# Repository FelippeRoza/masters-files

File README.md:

# masters-simulations

Files used in my master's program.

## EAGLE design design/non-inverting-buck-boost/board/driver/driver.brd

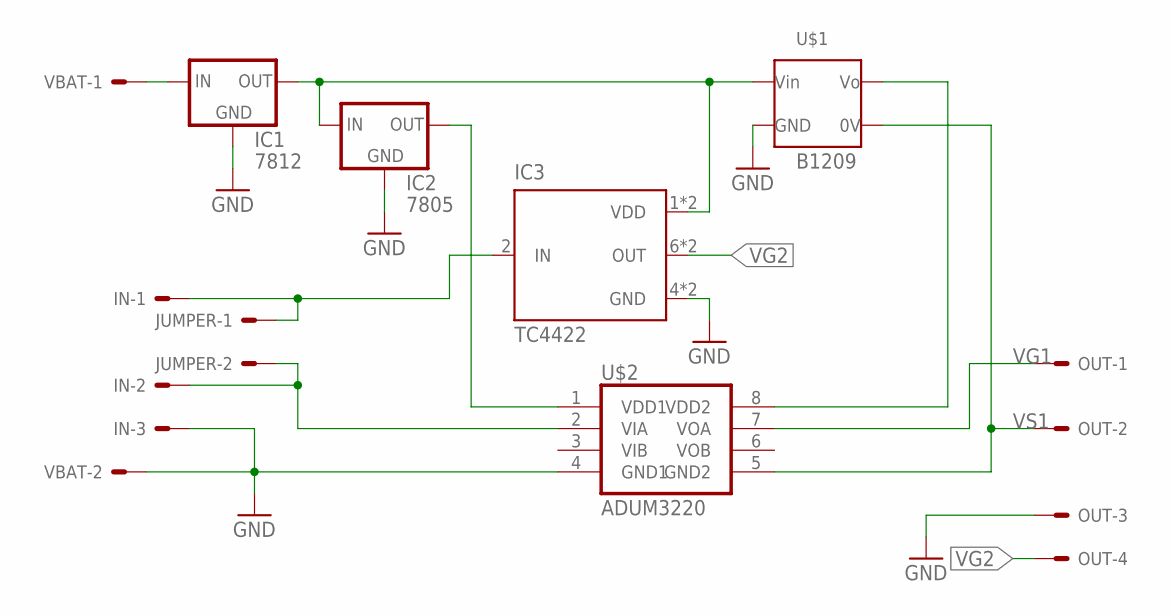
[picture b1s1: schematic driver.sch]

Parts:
IC1: 7812; 78XXS
IC2: 7805; 78XXS
IC3: TC4422; DIL08
IN: 22-23-2031
JUMPER: 22-23-2021
OUT: 22-23-2041
U$1: B1209; 22-23-2041
U$2: ADUM3220; SO8
VBAT: 22-23-2021

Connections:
5V: IC2.OUT, U$2.1 (VDD1)
12V: IC1.OUT, IC2.IN, IC3.1 (VDD), IC3.8 (VDD), U$1.2 (VIN)
GND: IC1.GND, IC2.GND, IC3.4 (GND), IC3.5 (GND), IN.3, OUT.3, U$1.1 (GND), U$2.4 (GND1), VBAT.2
unnamed: IC1.IN, VBAT.1
unnamed: IN.2, JUMPER.2, U$2.2 (VIA)
unnamed: IC3.2 (IN), IN.1, JUMPER.1
VDD2: U$1.4 (VO), U$2.8 (VDD2)
VG1: OUT.1, U$2.7 (VOA)
VG2: IC3.6 (OUT), IC3.7 (OUT), OUT.4
VS1: OUT.2, U$1.3 (0V), U$2.5 (GND2)

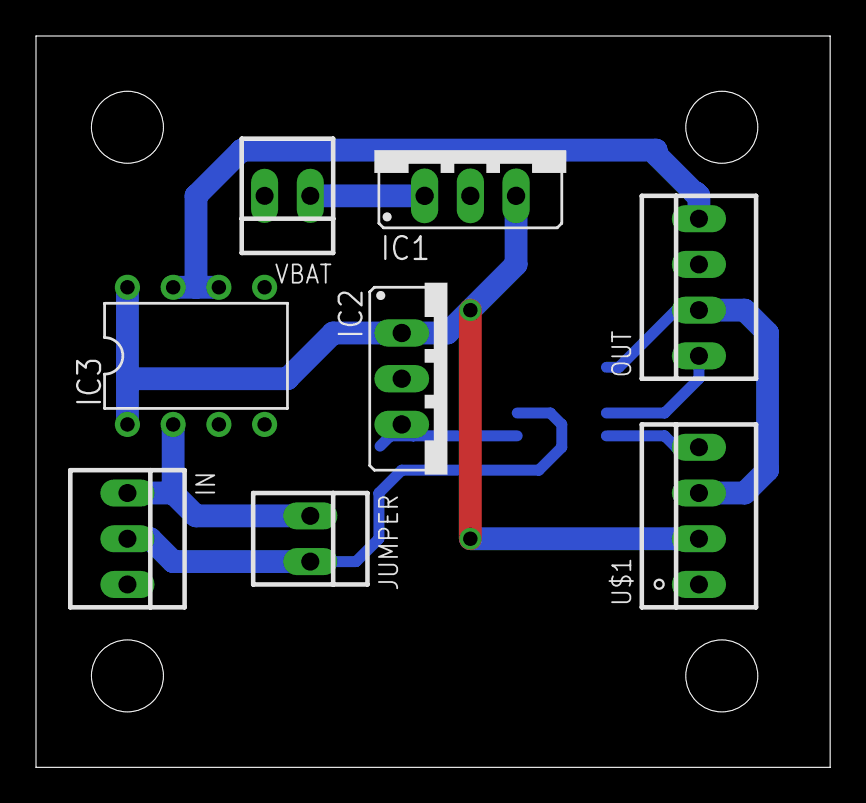
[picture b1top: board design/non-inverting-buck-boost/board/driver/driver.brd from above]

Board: 2 copper layers, 44.1 x 40.6 mm, 9 parts (1 on the bottom side), 10 nets.

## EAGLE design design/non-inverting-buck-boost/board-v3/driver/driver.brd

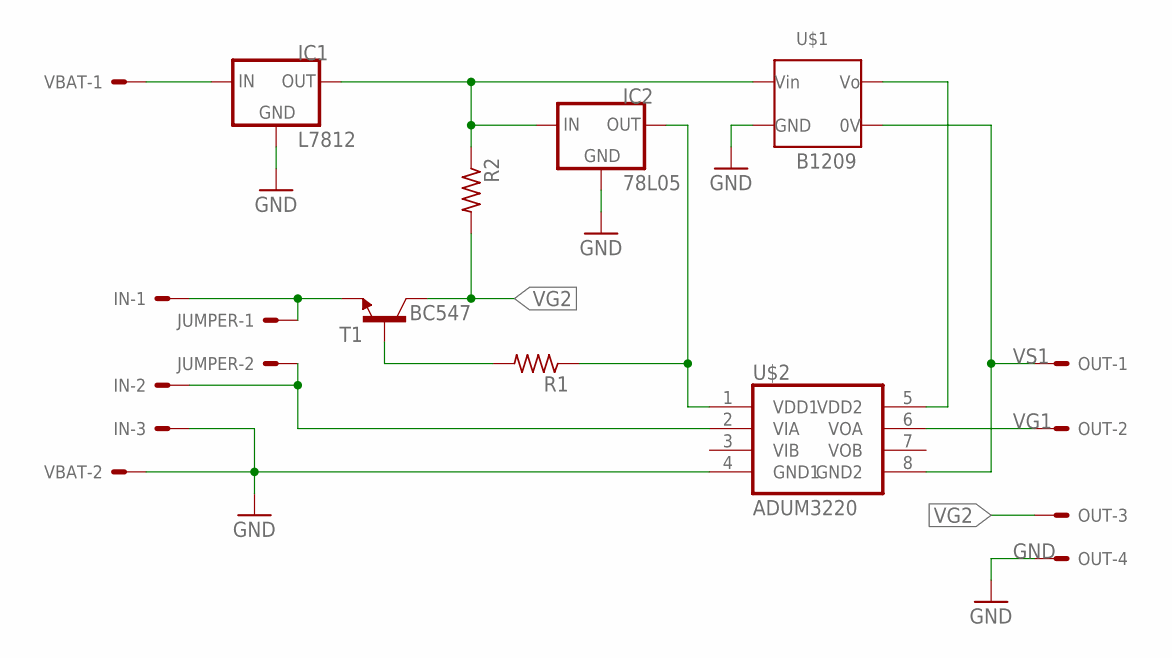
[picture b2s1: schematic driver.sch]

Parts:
IC1: L7812; 78XXL
IC2: 78L05; 78LXX
IN: 22-23-2031
JUMPER: 22-23-2021
OUT: 22-23-2041
R1, R2: R-US_0204/7; 0204/7
T1: BC547; TO92
U$1: B1209; 22-23-2041
U$2: ADUM3220; SO8
VBAT: 22-23-2021

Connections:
GND: IC1.GND, IC2.GND, IN.3, OUT.4, U$1.1 (GND), U$2.4 (GND1), VBAT.2
unnamed: IC1.OUT, IC2.IN, R2.1, U$1.2 (VIN)
unnamed: IC2.OUT, R1.1, U$2.1 (VDD1)
unnamed: R1.2, T1.2 (B)
unnamed: IC1.IN, VBAT.1
unnamed: IN.2, JUMPER.2, U$2.2 (VIA)
unnamed: IN.1, JUMPER.1, T1.1 (E)
VDD2: U$1.4 (VO), U$2.5 (VDD2)
VG1: OUT.2, U$2.6 (VOA)
VG2: OUT.3, R2.2, T1.3 (C)
VS1: OUT.1, U$1.3 (0V), U$2.8 (GND2)

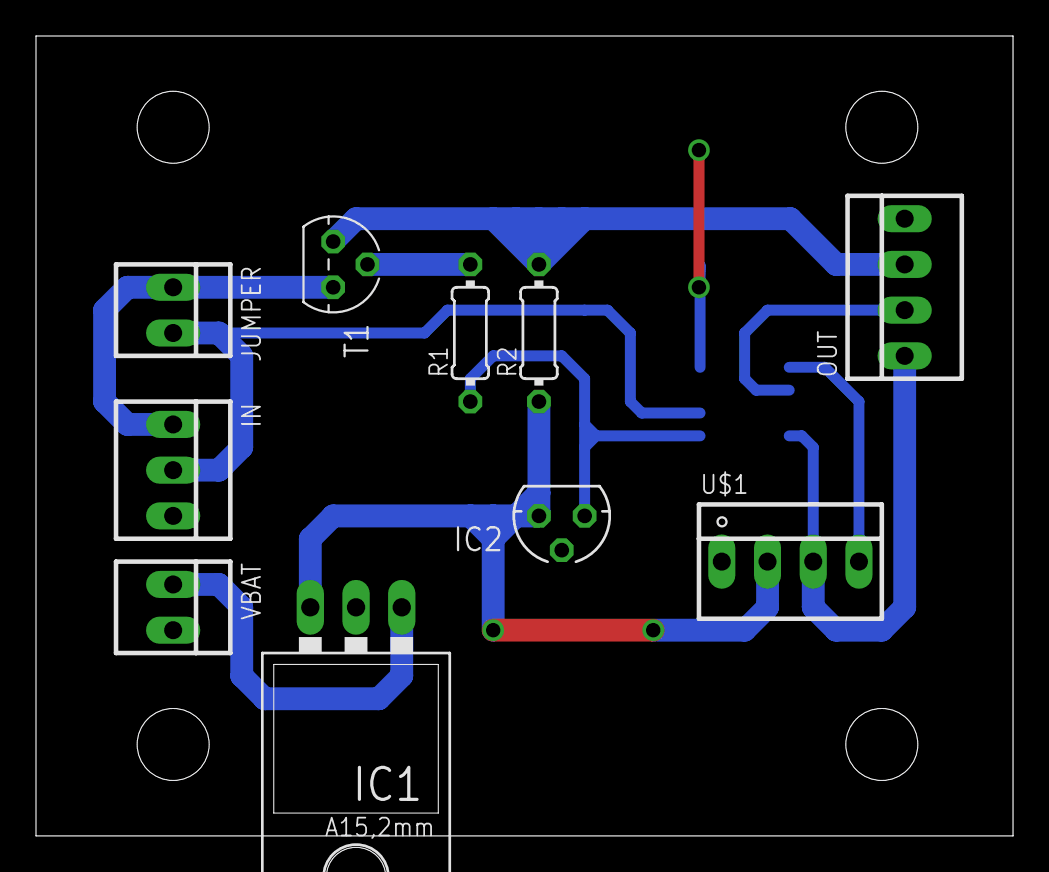
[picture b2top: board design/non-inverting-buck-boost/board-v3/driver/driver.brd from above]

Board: 2 copper layers, 54.3 x 44.4 mm, 11 parts (1 on the bottom side), 11 nets.

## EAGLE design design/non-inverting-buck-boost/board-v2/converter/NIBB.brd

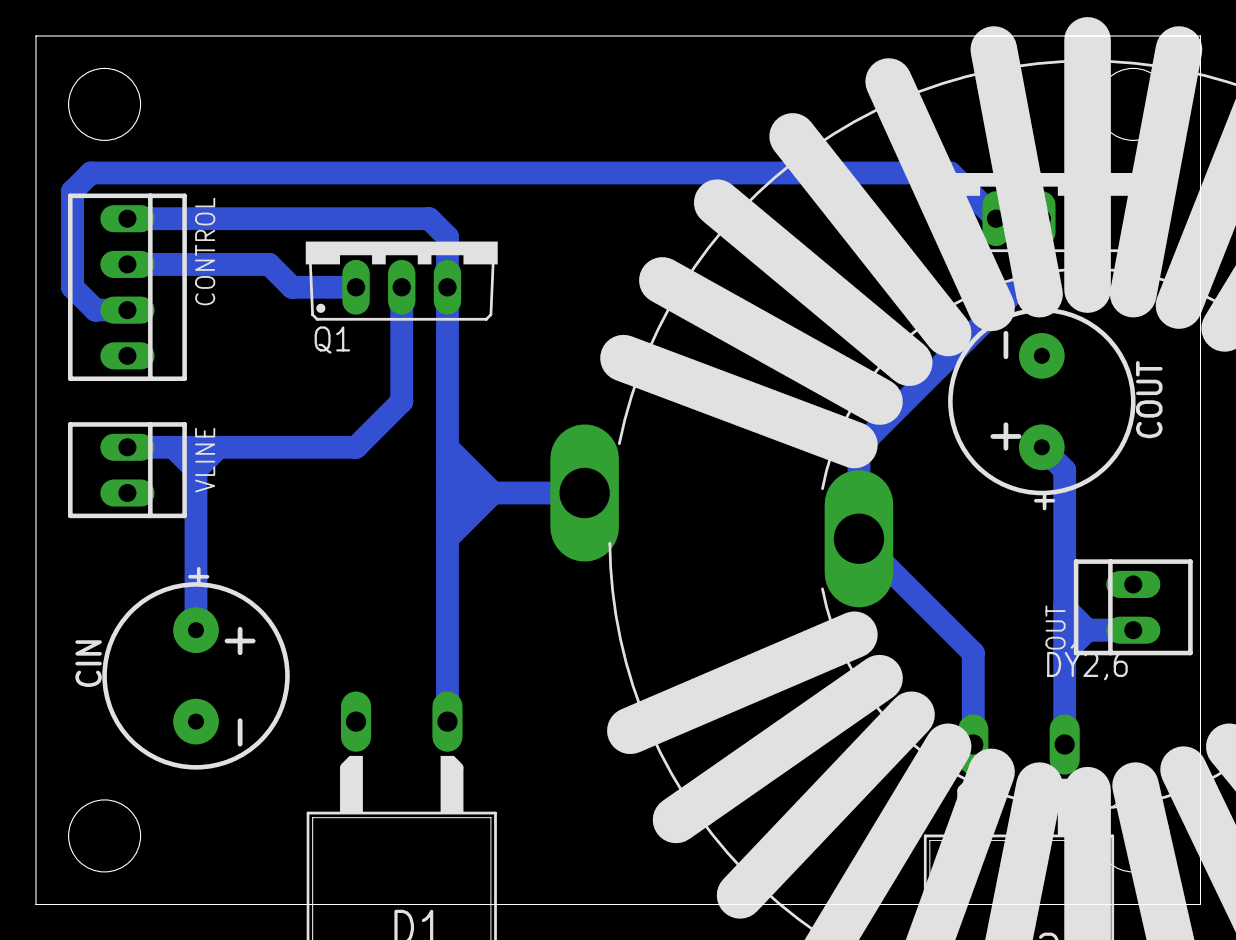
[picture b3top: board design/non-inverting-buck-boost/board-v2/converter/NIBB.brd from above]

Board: 2 copper layers, 64.7 x 48.2 mm, 10 parts (0 on the bottom side), 7 nets.

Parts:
CIN: 20ROUND40P
CONTROL: 22-23-2041
COUT: 20ROUND40P
D1, D2: MUR820; C221B1A
L1: RKE16
OUT: 22-23-2021
Q1, Q2: TO220BV
VLINE: 22-23-2021

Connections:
GND: CIN.-, CONTROL.4, COUT.-, D1.A, OUT.2, Q2.S, VLINE.2
unnamed: CONTROL.1, D1.C, L1.1, Q1.S
unnamed: D2.A, L1.2, Q2.D
unnamed: CIN.+, Q1.D, VLINE.1
unnamed: CONTROL.2, Q1.G
unnamed: CONTROL.3, Q2.G
unnamed: COUT.+, D2.C, OUT.1

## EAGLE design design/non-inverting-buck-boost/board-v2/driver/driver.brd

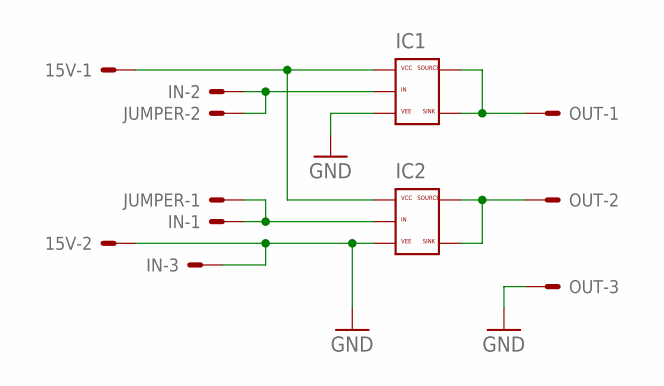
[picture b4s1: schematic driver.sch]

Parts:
15V: 22-23-2021
IC1, IC2: ZXGD3006E6; SOT23
IN: 22-23-2031
JUMPER: 22-23-2021
OUT: 22-23-2031

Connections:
15V+: 15V.1, IC1.1 (VCC), IC2.1 (VCC)
GND: 15V.2, IC1.3 (VEE), IC2.3 (VEE), IN.3, OUT.3
IN1: IC2.2 (IN), IN.1, JUMPER.1
IN2: IC1.2 (IN), IN.2, JUMPER.2
unnamed: IC1.4 (SINK), IC1.6 (SOURCE), OUT.1
unnamed: IC2.4 (SINK), IC2.6 (SOURCE), OUT.2

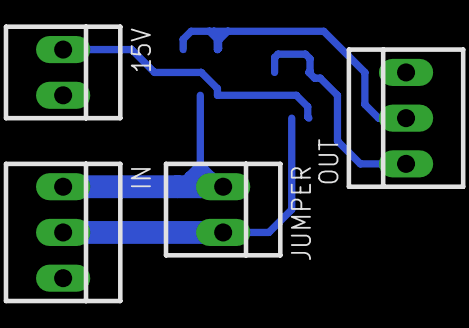
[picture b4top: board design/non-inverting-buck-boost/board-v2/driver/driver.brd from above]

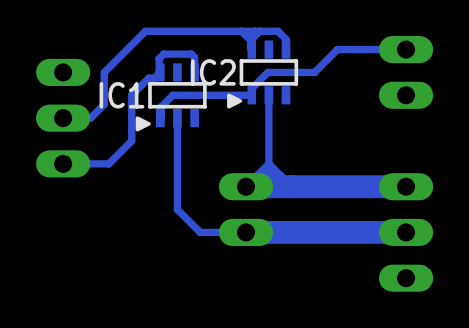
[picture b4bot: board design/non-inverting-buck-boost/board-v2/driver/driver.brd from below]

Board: 2 copper layers, 6 parts (2 on the bottom side), 6 nets.

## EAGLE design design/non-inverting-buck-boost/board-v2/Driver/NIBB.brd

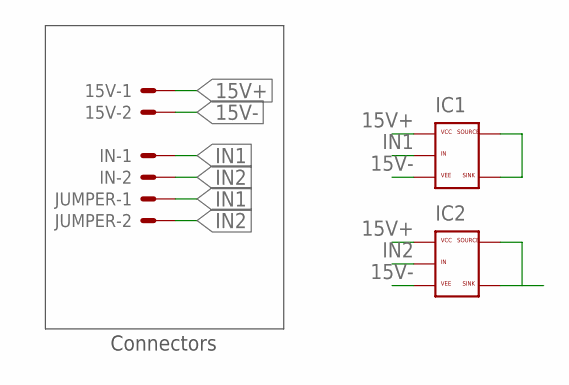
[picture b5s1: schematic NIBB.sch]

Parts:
15V: 22-23-2021
IC1, IC2: ZXGD3006E6; SOT23
IN: 22-23-2021
JUMPER: 22-23-2021

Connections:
15V+: 15V.1, IC1.1 (VCC), IC2.1 (VCC)
15V-: 15V.2, IC1.3 (VEE), IC2.3 (VEE)
IN1: IC1.2 (IN), IN.1, JUMPER.1
IN2: IC2.2 (IN), IN.2, JUMPER.2
unnamed: IC1.4 (SINK), IC1.6 (SOURCE)
unnamed: IC2.4 (SINK), IC2.6 (SOURCE)

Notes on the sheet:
Connectors

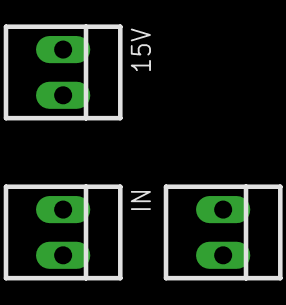
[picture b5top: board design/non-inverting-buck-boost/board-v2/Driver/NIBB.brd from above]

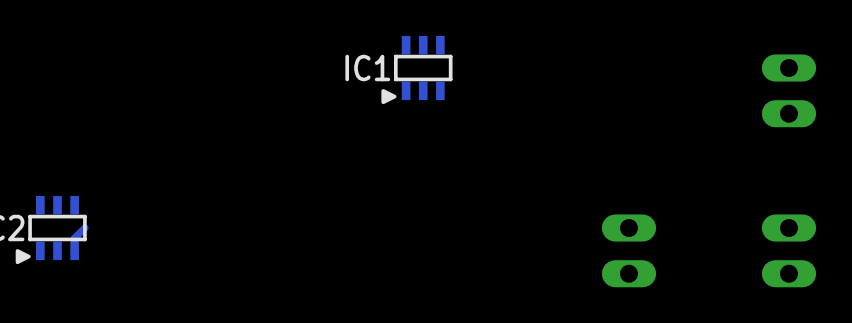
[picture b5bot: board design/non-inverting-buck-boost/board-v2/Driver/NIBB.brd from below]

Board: 2 copper layers, 5 parts (2 on the bottom side), 6 nets.

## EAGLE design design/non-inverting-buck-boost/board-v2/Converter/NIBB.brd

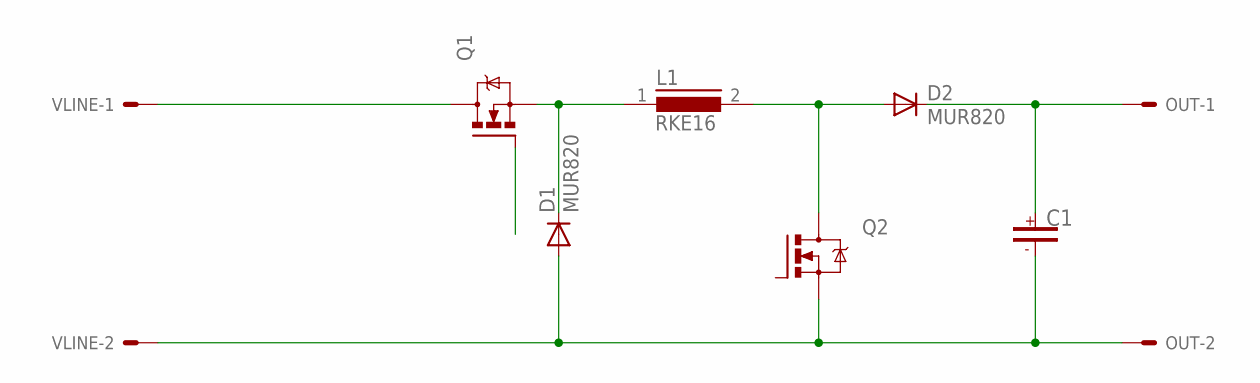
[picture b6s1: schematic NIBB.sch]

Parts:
C1: CAPP-UF; 20ROUND40P
D1, D2: MUR820; C221B1A
L1: RKE16
OUT: 22-23-2021
Q1, Q2: IRF640; TO220BV
VLINE: 22-23-2021

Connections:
unnamed: D1.C, L1.1, Q1.S
unnamed: D2.A, L1.2, Q2.D
unnamed: Q1.D, VLINE.1
unnamed: C1.-, D1.A, OUT.2, Q2.S, VLINE.2
unnamed: C1.+, D2.C, OUT.1

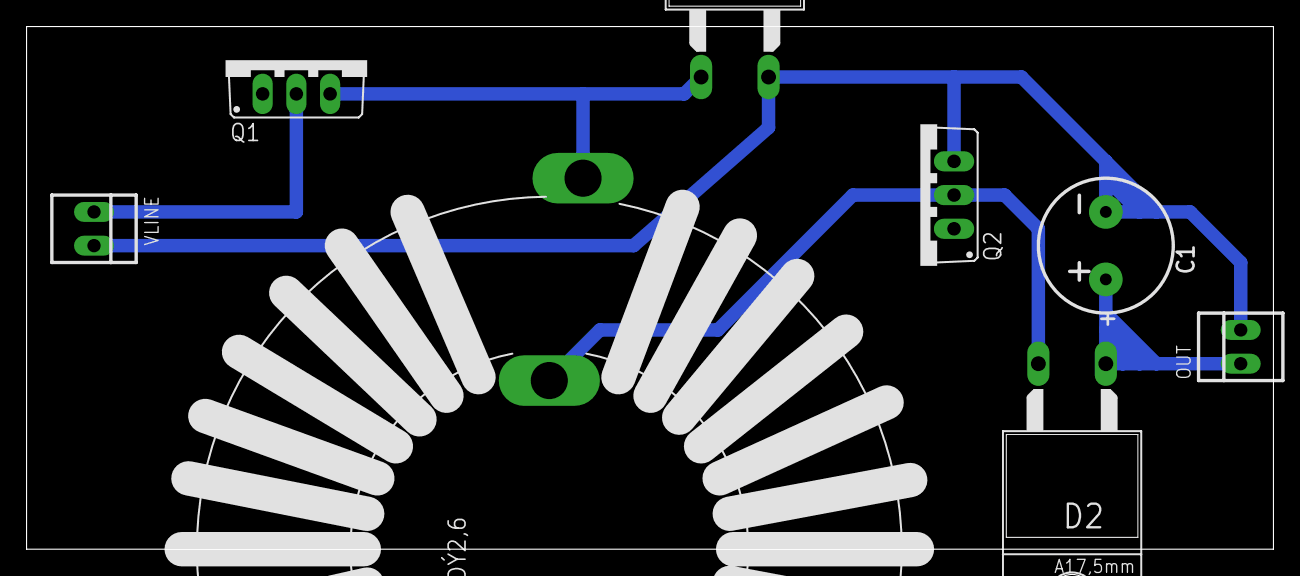
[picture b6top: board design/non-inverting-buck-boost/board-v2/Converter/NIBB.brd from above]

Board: 2 copper layers, 93.9 x 39.4 mm, 8 parts (0 on the bottom side), 5 nets.

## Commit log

2017-05-18 First simulation
2017-05-18 Added gitgnore
2017-05-19 Inductance changed - now it works
2017-05-19 fixed .gitgnore
2017-05-19 gitignore typo
2017-05-19 added noninverting buck-boost with generator simulation
2017-05-19 updated NIBB-generator
2017-05-19 added noninverting buck-boost with generator and turbine simulation
2017-05-19 added koford-412 simulation
2017-05-21 update koford generator simulation model
2017-05-21 update turbine simulation model
2017-05-23 updated generator model
2017-05-24 folders structural changes
2017-05-24 added design calculation sheet
2017-05-24 changed nomenclatures
2017-05-26 identation adjusts
2017-05-26 nomenclature update
2017-05-26 added absolute ripples
2017-05-26 added capacitor design
2017-05-26 typo
2017-05-26 added transistor maximum ratings
2017-05-27 changed capacitor formula
2017-05-27 updated components values
2017-05-30 changed capacitance
2017-05-30 changed output capacitor formula
2017-06-01 added new capacitance formula
2017-06-05 updated capacitance
2017-06-15 switches and diodes design calculations
2017-07-03 updated gitignore
2017-07-03 added schematic design file
2017-07-03 added board file
2017-07-11 added switches
2017-07-12 added connectors
2017-07-12 updated connectors
2017-07-12 added output capacitor and connector
2017-07-13 replaced fets
2017-07-13 added components to layout
2017-07-14 finished v1 layout
2017-07-14 added v2
2017-07-16 finished power board layout
2017-07-17 finished driver board layout
2017-07-17 updated folder names
2017-07-18 updated design rules
2017-08-14 updated mosfet conections
2017-08-14 added drill holes
2017-08-18 revert commit
2017-08-18 converter v3 - connector for isolated mosfet driver
2017-08-21 added arduino 20khz pwm file
2017-08-23 added inductor design project
2017-08-23 added simulation file
2017-08-24 arduino DAQ files added
2017-08-28 updated arduino pins on simulink file
2017-08-28 adapted code to run in Arduino nano
2017-08-29 created new driver schematic file
2017-08-29 finished driver schematic
2017-08-30 updated schematic - non inverting driver topology
2017-08-30 finished board layout
2017-08-31 fixed ADuM3220 pins
2017-09-04 removed reduntant files
2017-09-04 new driver design with 2 ADUM3220
2017-09-06 motor case FreeCAD file
2017-09-11 finished motor case design
2017-09-11 generated stl file
2017-09-11 increased case radius
2017-09-20 changed folder structure
2017-10-05 updated pwm pin
2017-10-06 changed non-isolated driver to TC4422
2017-11-08 added arduino interface to matlab
2017-11-30 included extra support to motor case
2017-12-05 bug fixed - TOC called before TIC
2017-12-07 some improvements in plotting data
2017-12-11 new test results
2017-12-11 added new test files
2017-12-12 added multiple plotting for last tests
2017-12-12 new test files and figures
2017-12-12 modified to plot both figures and added legend
2017-12-12 new figures with labels
2018-02-01 added matlab simulation for the wind power system
2018-02-02 renamed to avoid conflit with matlab inbuilt function
2018-02-19 added PSIM wind turbine model
2018-02-20 added first test plot functions
2018-02-21 added matlab script to fit turbine model using least squares
2018-03-01 files to generate figures for my thesis
2018-03-02 updated plot script and figures
2018-03-22 added plots for turbine model
2018-04-02 plots saved as eps files
2018-04-04 added new turbine model
2018-04-16 new plots
2018-04-18 updated plot
2018-04-28 voltage and current ripple plots
